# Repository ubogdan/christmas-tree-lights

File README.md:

# christmas-tree-lights
ESP8266 powered christmas tree lights (status: WIP)

Hardware
========

#### Requirements
 * 1x ESP8266 (D1 Mini) 
 * 1x WS2812b/SK6812 LED Strip or "_Neopixel_" LED Strip
 * 1x 74HCT08 Quad AND gate 
 * 4x 100nF capacitor
 * 1x 1N4148 diode or similar
 * 1x 400ohm rezistor

This is printed circuit preview.  

The project includes the [board](/eagle/schematic.brd) and [schematic](/eagle/schematic.sch) for Eagle CAD. You may 
need to download the following library if you want to edit the cad files.

 * [ESP8266 Eagle Library](https://github.com/wvanvlaenderen/ESP8266-Eagle_Library) used in schematic.

#### Testing the hardware
* Adjust the PixelCount from sketch with the number of leds of the strip you are going to use. 
* Upload hardware-test.ino into d1 using Aduino.
* The program should light up all leds in the follwing order Red , Green , Blue. In the event of Green si reversed with
 Blue you shoud replace  
```
NeoPixelBus<NeoRgbFeature, Neo800KbpsMethod> strip(PixelCount, PixelPin);
```
with 
```
NeoPixelBus<NeoGrbFeature, Neo800KbpsMethod> strip(PixelCount, PixelPin);
```

Software
========
I'm going to use Arduino as programing 

Libraries
  * NeoPixelBus https://github.com/Makuna/NeoPixelBus
  * ESP8266WiFi https://github.com/esp8266/Arduino
  * WiFiManager, https://github.com/tzapu/WiFiManager
  * ESP8266mDNS.h, https://github.com/esp8266/Arduino/tree/master/libraries/ESP8266mDNS

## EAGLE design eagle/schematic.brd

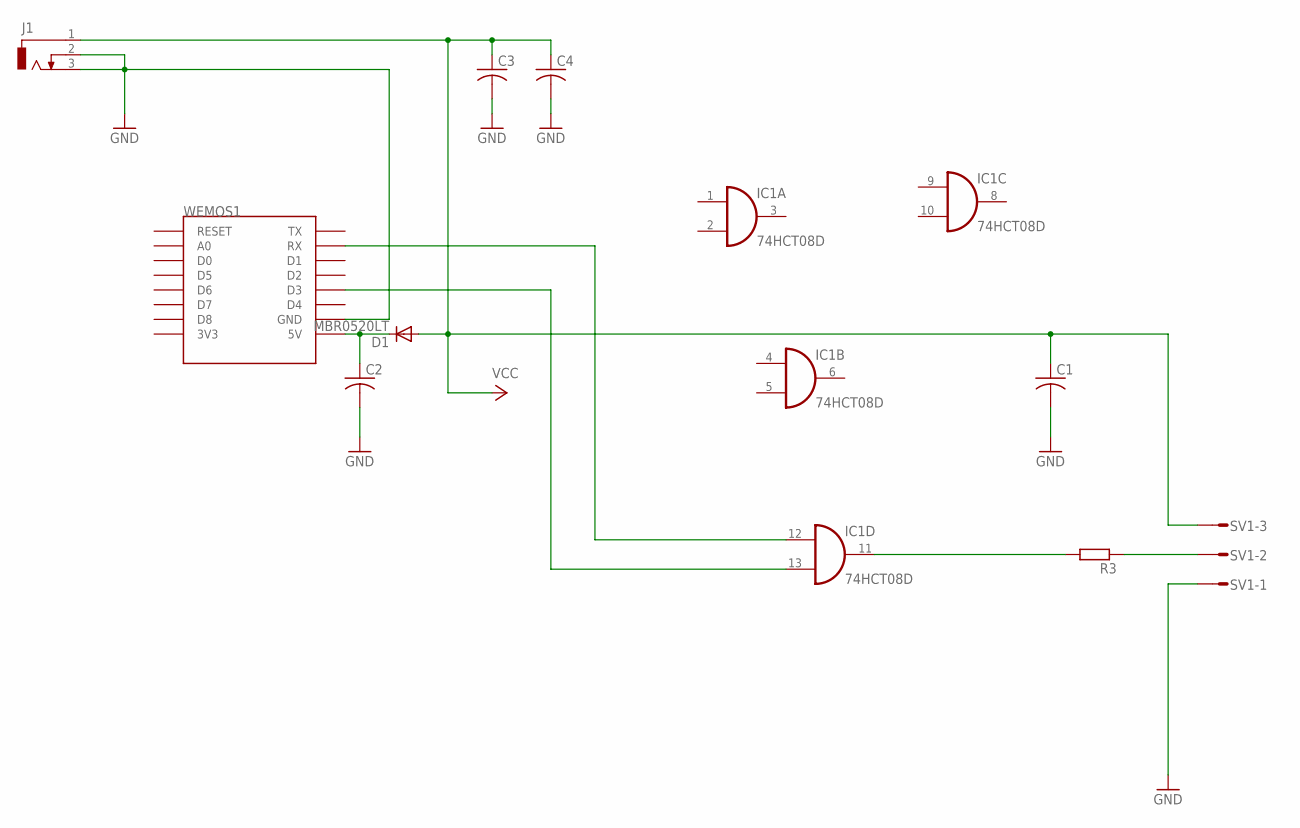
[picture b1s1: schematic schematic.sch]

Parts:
C1, C2, C3, C4: C-USC1206; C1206
D1: MBR0520LT; SOD123
IC1: 74HCT08D; SO14
J1: DCJ0303
R3: R-EU_M1206; M1206
SV1: S03P
WEMOS1: WEMOS-D1-MINI

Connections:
GND: C1.2, C2.2, C3.2, C4.2, IC1.7 (GND), J1.2, J1.3, SV1.1, WEMOS1.GND
unnamed: R3.1, SV1.2
unnamed: C2.1, D1.C, WEMOS1.5V
unnamed: IC1.11 (O), R3.2
unnamed: IC1.12 (I0), WEMOS1.RX
unnamed: IC1.13 (I1), WEMOS1.D3
VCC: C1.1, C3.1, C4.1, D1.A, IC1.14 (VCC), J1.1, SV1.3

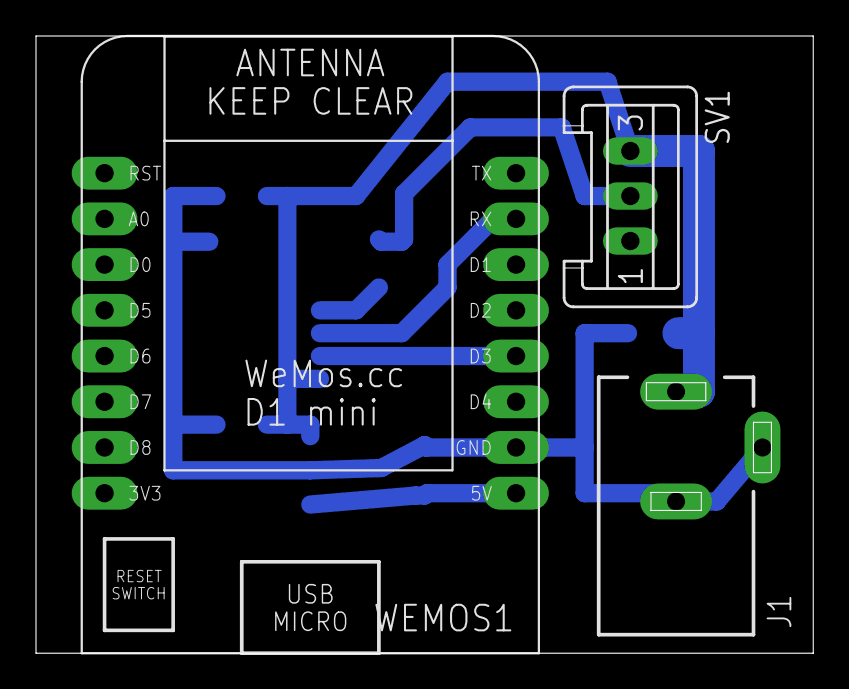
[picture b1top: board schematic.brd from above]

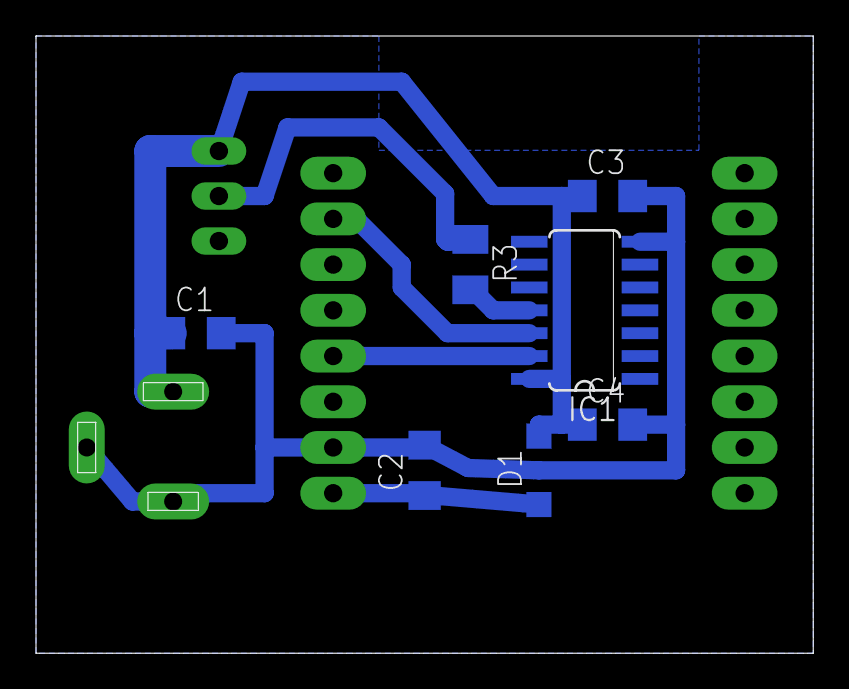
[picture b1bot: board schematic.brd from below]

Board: 2 copper layers, 43.2 x 34.3 mm, 10 parts (7 on the bottom side), 7 nets.

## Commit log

2019-12-07 Add hardware test code.
